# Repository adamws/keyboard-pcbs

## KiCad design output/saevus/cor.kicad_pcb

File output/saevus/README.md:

## saevus/cor

[layout](cor-kle.json) - [PCB](cor.kicad_pcb)

{:loading="lazy"}

[Open in keyboard-layout-editor](http://www.keyboard-layout-editor.com/##@@_c=#777777;&=0,0&_x:0.25;&=0,1&_c=#cccccc;&=0,2&=0,3&=0,4&=0,5&=0,6&=0,7&=0,8&=0,9&=0,10&=0,11&=0,12&=0,13&_c=#aaaaaa&w:2;&=0,14%0A%0A%0A0,0&_x:0.5;&=0,16;&@_c=#777777;&=1,0&_x:0.25&c=#aaaaaa&w:1.5;&=1,1&_c=#cccccc;&=1,2&=1,3&=1,4&=1,5&=1,6&=1,7&=1,8&=1,9&=1,10&=1,11&=1,12&=1,13&_w:1.5;&=1,15&_x:0.5&c=#aaaaaa;&=1,16;&@_c=#777777;&=2,0&_x:0.25&c=#aaaaaa&w:1.75;&=2,1&_c=#cccccc;&=2,2&=2,3&=2,4&=2,5&=2,6&=2,7&=2,8&=2,9&=2,10&=2,11&=2,12&_c=#777777&w:2.25;&=2,14&_x:0.5&c=#aaaaaa;&=2,16;&@_c=#777777;&=3,0&_x:0.25&c=#aaaaaa&w:2.25;&=3,1&_c=#cccccc;&=3,3&=3,4&=3,5&=3,6&=3,7&=3,8&=3,9&=3,10&=3,11&=3,12&_c=#aaaaaa&w:1.75;&=3,13&_x:1.5;&=3,16;&@_x:15.5&y:-0.75&c=#777777;&=3,15;&@_y:-0.25;&=4,0&_x:0.25&c=#aaaaaa&w:1.25;&=4,1%0A%0A%0A1,0&_w:1.25;&=4,2%0A%0A%0A1,0&_w:1.25;&=4,3%0A%0A%0A1,0&_c=#cccccc&w:6.25;&=4,7%0A%0A%0A1,0&_c=#aaaaaa&w:1.25;&=4,11%0A%0A%0A1,0&_w:1.25;&=4,12%0A%0A%0A1,0;&@_x:14.5&y:-0.75&c=#777777;&=4,14&=4,15&=4,16;&@_x:18.0&y:-5.25&c=#aaaaaa;&=0,14%0A%0A%0A0,1&=0,15%0A%0A%0A0,1;&@_x:1.25&y:4.25&w:1.5;&=4,1%0A%0A%0A1,1&=4,2%0A%0A%0A1,1&_w:1.5;&=4,3%0A%0A%0A1,1&_c=#cccccc&w:7;&=4,7%0A%0A%0A1,1&_c=#aaaaaa&w:1.5;&=4,12%0A%0A%0A1,1)

{:loading="lazy"}

## saevus/cor_tkl

[layout](cor_tkl-kle.json) - [PCB](cor_tkl.kicad_pcb)

{:loading="lazy"}

[Open in keyboard-layout-editor](http://www.keyboard-layout-editor.com/##@@_c=#777777;&=0,0&_x:0.25&c=#aaaaaa;&=0,1&=0,2&=0,3&=0,4&_x:0.25;&=0,5&=0,6&=0,7&=0,8&_x:0.25;&=0,9&=0,10&=0,11&=0,12&_x:0.25;&=0,13&_x:0.25;&=0,14&=0,15&=0,16;&@_y:0.25&c=#cccccc;&=1,0&=1,1&=1,2&=1,3&=1,4&=1,5&=1,6&=1,7&=1,8&=1,9&=1,10&=1,11&=1,12&_c=#aaaaaa&w:2;&=1,13%0A%0A%0A0,0&_x:0.25;&=1,14&=1,15&=1,16;&@_w:1.5;&=2,0&_c=#cccccc;&=2,1&=2,2&=2,3&=2,4&=2,5&=2,6&=2,7&=2,8&=2,9&=2,10&=2,11&=2,12&_w:1.5;&=2,13%0A%0A%0A1,0&_x:0.25&c=#aaaaaa;&=2,14&=2,15&=2,16;&@_w:1.75;&=3,0&_c=#cccccc;&=3,1&=3,2&=3,3&=3,4&=3,5&=3,6&=3,7&=3,8&=3,9&=3,10&=3,11&_c=#777777&w:2.25;&=3,12%0A%0A%0A1,0;&@_c=#aaaaaa&w:2.25;&=4,0%0A%0A%0A2,0&_c=#cccccc;&=4,2&=4,3&=4,4&=4,5&=4,6&=4,7&=4,8&=4,9&=4,10&=4,11&_c=#aaaaaa&w:2.75;&=4,12%0A%0A%0A3,0&_x:1.25&c=#777777;&=4,15;&@_c=#aaaaaa&w:1.25;&=5,0%0A%0A%0A4,0&_w:1.25;&=5,1%0A%0A%0A4,0&_w:1.25;&=5,2%0A%0A%0A4,0&_c=#cccccc&w:6.25;&=5,7%0A%0A%0A4,0&_c=#aaaaaa&w:1.25;&=5,10%0A%0A%0A4,0&_w:1.25;&=5,11%0A%0A%0A4,0&_w:1.25;&=5,12%0A%0A%0A4,0&_w:1.25;&=5,13%0A%0A%0A4,0&_x:0.25&c=#777777;&=5,14&=5,15&=5,16;&@_x:13&y:0.25&c=#aaaaaa;&=1,13%0A%0A%0A0,1&=3,13%0A%0A%0A0,1;&@_x:13.75&c=#777777&w:1.25&h:2&w2:1.5&h2:1&x2:-0.25;&=2,13%0A%0A%0A1,1;&@_x:12.75&c=#cccccc;&=3,12%0A%0A%0A1,1;&@_c=#aaaaaa&w:1.25;&=4,0%0A%0A%0A2,1&_c=#cccccc;&=4,1%0A%0A%0A2,1&_x:10.0&c=#aaaaaa&w:1.75;&=4,12%0A%0A%0A3,1&=4,13%0A%0A%0A3,1;&@_w:1.5;&=5,0%0A%0A%0A4,1&=5,1%0A%0A%0A4,1&_w:1.5;&=5,2%0A%0A%0A4,1&_c=#cccccc&w:7;&=5,7%0A%0A%0A4,1&_c=#aaaaaa&w:1.5;&=5,11%0A%0A%0A4,1&=5,12%0A%0A%0A4,1&_w:1.5;&=5,13%0A%0A%0A4,1;&@_w:1.5;&=5,0%0A%0A%0A4,2&_d:true;&=5,1%0A%0A%0A4,2&_w:1.5;&=5,2%0A%0A%0A4,2&_c=#cccccc&w:7;&=5,7%0A%0A%0A4,2&_c=#aaaaaa&w:1.5;&=5,11%0A%0A%0A4,2&_d:true;&=5,12%0A%0A%0A4,2&_w:1.5;&=5,13%0A%0A%0A4,2)

{:loading="lazy"}

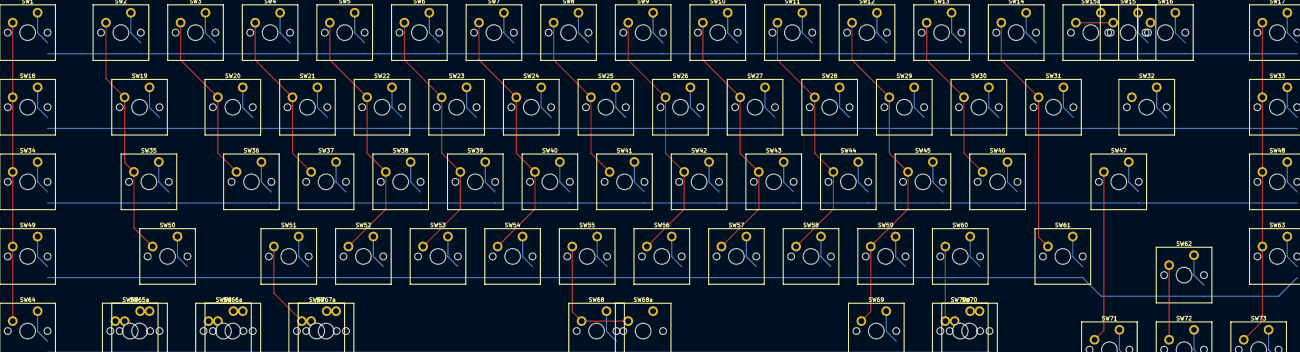
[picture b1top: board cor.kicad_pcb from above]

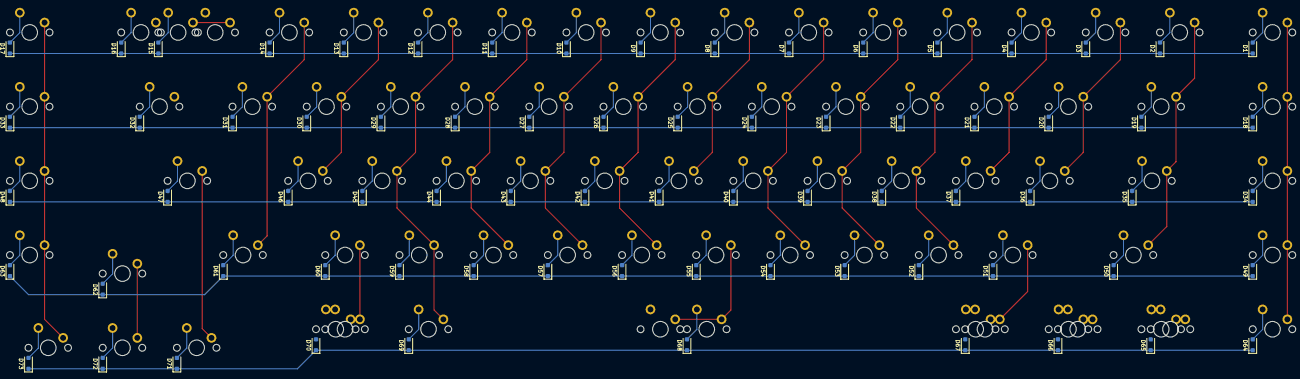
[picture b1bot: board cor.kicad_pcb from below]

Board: 2 copper layers, 152 parts (73 on the bottom side), 95 nets.

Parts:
D1, D2, D3, D4, D5, D6, D7, D8, D9, D10, D11, D12, D13, D14, D15, D16, D17, D18, D19, D20, D21, D22, D23, D24, D25, D26, D27, D28, D29, D30, D31, D32, D33, D34, D35, D36, D37, D38, D39, D40, D41, D42, D43, D44, D45, D46, D47, D48, D49, D50, D51, D52, D53, D54, D55, D56, D57, D58, D59, D60, D61, D62, D63, D64, D65, D66, D67, D68, D69, D70, D71, D72, D73: D_SOD-123F
SW1, SW2, SW3, SW4, SW5, SW6, SW7, SW8, SW9, SW10, SW11, SW12, SW13, SW14, SW15, SW15a, SW16, SW17, SW18, SW19, SW20, SW21, SW22, SW23, SW24, SW25, SW26, SW27, SW28, SW29, SW30, SW31, SW32, SW33, SW34, SW35, SW36, SW37, SW38, SW39, SW40, SW41, SW42, SW43, SW44, SW45, SW46, SW47, SW48, SW49, SW50, SW51, SW52, SW53, SW54, SW55, SW56, SW57, SW58, SW59, SW60, SW61, SW62, SW63, SW64, SW65, SW65a, SW66, SW66a, SW67, SW67a, SW68, SW68a, SW69, SW70, SW70a, SW71, SW72, SW73: SW_Cherry_MX_PCB_1.00u

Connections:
COL0: SW1.1, SW18.1, SW34.1, SW49.1, SW64.1
COL1: SW2.1, SW19.1, SW35.1, SW50.1, SW65.1, SW65a.1
COL2: SW3.1, SW20.1, SW36.1, SW66.1, SW66a.1
COL3: SW4.1, SW21.1, SW37.1, SW51.1, SW67.1, SW67a.1
COL4: SW5.1, SW22.1, SW38.1, SW52.1
COL5: SW6.1, SW23.1, SW39.1, SW53.1
COL6: SW7.1, SW24.1, SW40.1, SW54.1
COL7: SW8.1, SW25.1, SW41.1, SW55.1, SW68.1, SW68a.1
COL8: SW9.1, SW26.1, SW42.1, SW56.1
COL9: SW10.1, SW27.1, SW43.1, SW57.1
COL10: SW11.1, SW28.1, SW44.1, SW58.1
COL11: SW12.1, SW29.1, SW45.1, SW59.1, SW69.1
COL12: SW13.1, SW30.1, SW46.1, SW60.1, SW70.1, SW70a.1
COL13: SW14.1, SW31.1, SW61.1
COL14: SW15.1, SW15a.1, SW47.1, SW71.1
COL15: SW16.1, SW32.1, SW62.1, SW72.1
COL16: SW17.1, SW33.1, SW48.1, SW63.1, SW73.1
unnamed: D1.2, SW1.2
unnamed: D2.2, SW2.2
unnamed: D3.2, SW3.2
unnamed: D4.2, SW4.2
unnamed: D5.2, SW5.2
unnamed: D6.2, SW6.2
unnamed: D7.2, SW7.2
unnamed: D8.2, SW8.2
unnamed: D9.2, SW9.2
unnamed: D10.2, SW10.2
unnamed: D11.2, SW11.2
unnamed: D12.2, SW12.2
unnamed: D13.2, SW13.2
unnamed: D14.2, SW14.2
unnamed: D15.2, SW15.2, SW15a.2
unnamed: D16.2, SW16.2
unnamed: D17.2, SW17.2
unnamed: D18.2, SW18.2
unnamed: D19.2, SW19.2
unnamed: D20.2, SW20.2
unnamed: D21.2, SW21.2
unnamed: D22.2, SW22.2
unnamed: D23.2, SW23.2
unnamed: D24.2, SW24.2
unnamed: D25.2, SW25.2
unnamed: D26.2, SW26.2
unnamed: D27.2, SW27.2
unnamed: D28.2, SW28.2
unnamed: D29.2, SW29.2
unnamed: D30.2, SW30.2
unnamed: D31.2, SW31.2
unnamed: D32.2, SW32.2
unnamed: D33.2, SW33.2
unnamed: D34.2, SW34.2
unnamed: D35.2, SW35.2
unnamed: D36.2, SW36.2
unnamed: D37.2, SW37.2
unnamed: D38.2, SW38.2
unnamed: D39.2, SW39.2
unnamed: D40.2, SW40.2
unnamed: D41.2, SW41.2
unnamed: D42.2, SW42.2
unnamed: D43.2, SW43.2
unnamed: D44.2, SW44.2
unnamed: D45.2, SW45.2
unnamed: D46.2, SW46.2
unnamed: D47.2, SW47.2
unnamed: D48.2, SW48.2
unnamed: D49.2, SW49.2
unnamed: D50.2, SW50.2
unnamed: D51.2, SW51.2
unnamed: D52.2, SW52.2
unnamed: D53.2, SW53.2
unnamed: D54.2, SW54.2
unnamed: D55.2, SW55.2
unnamed: D56.2, SW56.2
unnamed: D57.2, SW57.2
unnamed: D58.2, SW58.2
unnamed: D59.2, SW59.2
unnamed: D60.2, SW60.2
unnamed: D61.2, SW61.2
unnamed: D62.2, SW62.2
unnamed: D63.2, SW63.2
unnamed: D64.2, SW64.2
unnamed: D65.2, SW65.2, SW65a.2
unnamed: D66.2, SW66.2, SW66a.2
unnamed: D67.2, SW67.2, SW67a.2
unnamed: D68.2, SW68.2, SW68a.2
unnamed: D69.2, SW69.2
unnamed: D70.2, SW70.2, SW70a.2
unnamed: D71.2, SW71.2
unnamed: D72.2, SW72.2
unnamed: D73.2, SW73.2
ROW0: D1.1, D2.1, D3.1, D4.1, D5.1, D6.1, D7.1, D8.1, D9.1, D10.1, D11.1, D12.1, D13.1, D14.1, D15.1, D16.1, D17.1
ROW1: D18.1, D19.1, D20.1, D21.1, D22.1, D23.1, D24.1, D25.1, D26.1, D27.1, D28.1, D29.1, D30.1, D31.1, D32.1, D33.1
ROW2: D34.1, D35.1, D36.1, D37.1, D38.1, D39.1, D40.1, D41.1, D42.1, D43.1, D44.1, D45.1, D46.1, D47.1, D48.1
ROW3: D49.1, D50.1, D51.1, D52.1, D53.1, D54.1, D55.1, D56.1, D57.1, D58.1, D59.1, D60.1, D61.1, D62.1, D63.1
ROW4: D64.1, D65.1, D66.1, D67.1, D68.1, D69.1, D70.1, D71.1, D72.1, D73.1
